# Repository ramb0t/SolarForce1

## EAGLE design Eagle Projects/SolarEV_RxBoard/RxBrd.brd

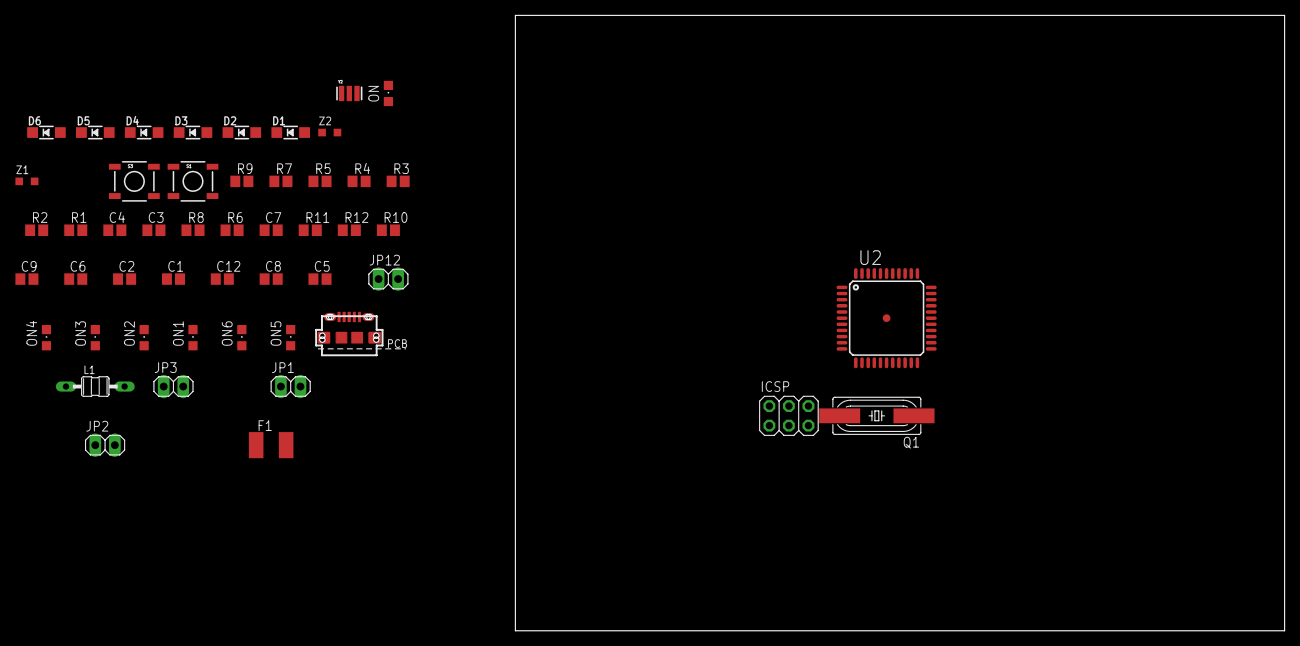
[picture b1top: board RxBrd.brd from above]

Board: 2 copper layers, 100.0 x 80.0 mm, 50 parts (0 on the bottom side), 34 nets, no tracks yet.

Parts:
C1, C2, C6, C9: 100n; C0805
C3, C4: 22p; C0805
C5: 100nF; C0805
C7: 1uF; C0805
C8, C12: 10uF; C0805
D1, D2, D3, D4, D5, D6: MBR0540; SOD123@2
F1: MF-MSMF050-2 500mA; L1812
ICSP: ICSP; 2X03
J1: USB MICRO; CON2_USB_MICRO_B_AT
JP1: Anemometer Connect; 1X02
JP2: PhotovoltaicCell Connect; 1X02
JP3: RF Link Connect; 1X02
JP12: 1X02
L1: 10uH; MMICC7
ON: Red; CHIPLED_0805
ON1, ON2, ON3, ON4: Green; CHIPLED_0805
ON5, ON6: Yellow; CHIPLED_0805
Q1: HC49UP
R1: 1M; R0805
R2, R3, R7, R9, R10, R11, R12: 1k; R0805
R4, R5: 22; R0805
R6: 51k; R0805
R8: 10k; R0805
S1, S3: RESET; TACTILE_SWITCH_SMD
U2: ATMEGA32U4-XUAU; TQFP44-PAD
Y2: 16MHz; RESONATOR
Z1, Z2: CG0603MLC-05E; CT/CN0603

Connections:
+5V: C1.1, C2.1, C12.1, D1.C, D2.C, D3.C, D5.C, JP1.2, JP12.1, L1.1, R2.2, R3.2, R6.2, R7.2, R9.1, R10.1, R11.1, R12.2, U2.2, U2.14, U2.34
ANEMOMETER_CONNECTED_OK: ON2.C, U2.40
AREF: C6.1, U2.42
AVCC: C5.1, L1.2, U2.24, U2.44
D+: J1.P3, R5.1, Z1.1
D-: J1.P2, R4.1, Z2.1
GND: C1.2, C2.2, C3.2, C4.2, C5.2, C6.2, C7.2, C8.2, C9.2, C12.2, D4.A, D6.A, ICSP.6, J1.P5, J1.S1, J1.S2, J1.S3, J1.S4, J1.S5, J1.S6, JP2.2, JP12.2, ON.C, R8.1, S1.1, S1.2, S3.3, S3.4, U2.5, U2.15, U2.23, U2.35, U2.43, Y2.2, Z1.2, Z2.2
MISO: ICSP.1, U2.11
MOSI: ICSP.4, U2.10
unnamed: D3.A, D4.C, JP1.1, U2.25
unnamed: ON3.A, R7.1
unnamed: ON.A, R12.1
unnamed: D5.A, D6.C, JP2.1, U2.30
unnamed: R6.1, S1.3, S1.4, U2.13
unnamed: ON4.A, R9.2
unnamed: JP3.1, U2.20
unnamed: JP3.2, U2.21
unnamed: ON2.A, R3.1
unnamed: D2.A, ICSP.2
unnamed: ON1.A, R2.1
unnamed: ON5.A, R10.2
unnamed: ON6.A, R11.2
unnamed: ICSP.5, S3.1, S3.2
PC_CONNECTED_OK: ON1.C, U2.41
PHOTOCELL_CONNECTED_OK: ON3.C, U2.39
RD+: R5.2, U2.4
RD-: R4.2, U2.3
RF_TRANSCEIVER_CONNECTED_OK: ON4.C, U2.1
SCK: ICSP.3, U2.9
UCAP: C7.1, U2.6
VUSB: C8.1, C9.1, D1.A, F1.1, R8.2, U2.7
XTAL1: C4.1, Q1.1, R1.1, U2.17, Y2.3
XTAL2: C3.1, Q1.2, R1.2, U2.16, Y2.1
XUSB: F1.2, J1.P1

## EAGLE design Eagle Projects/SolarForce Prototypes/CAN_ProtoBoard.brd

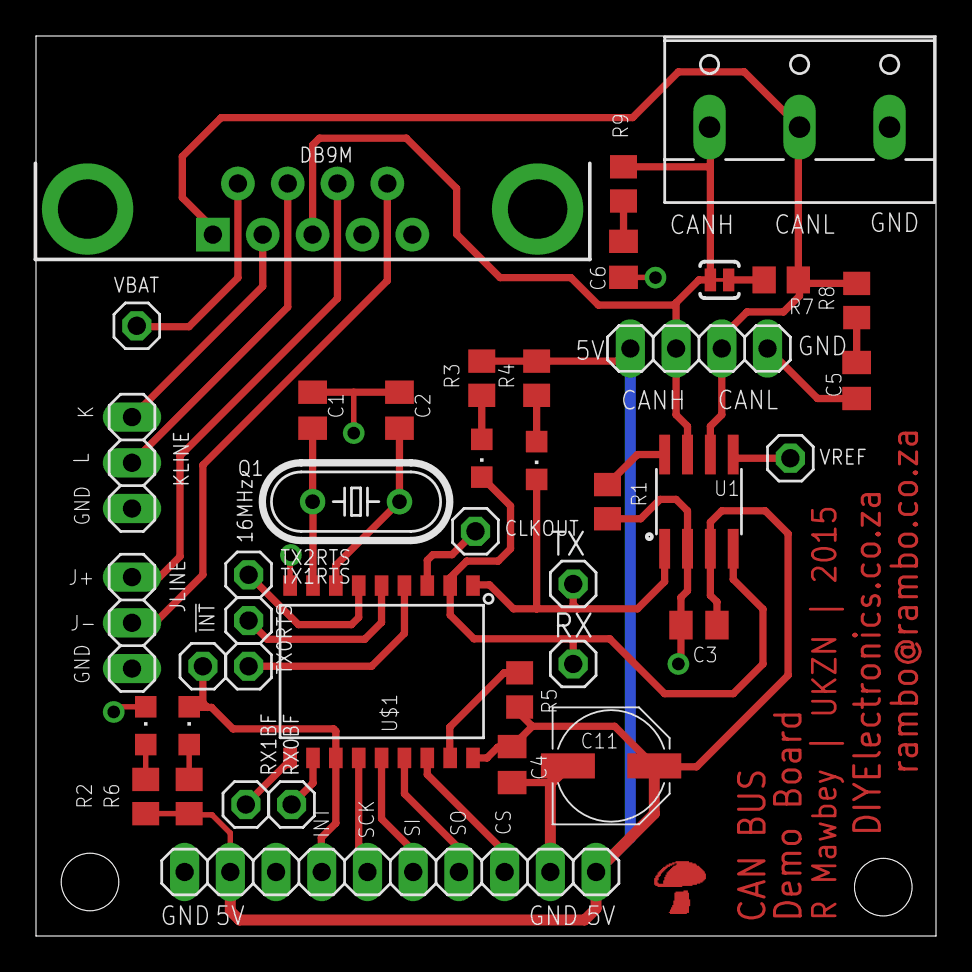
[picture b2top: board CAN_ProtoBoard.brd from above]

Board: 2 copper layers, 50.0 x 50.0 mm, 41 parts (0 on the bottom side), 34 nets.

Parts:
!INT: 1X01
C1, C2: 22pF; C0805K
C3, C4: 100nF; C0805K
C5, C6: 560pF; C0805K
C11: 100uF; PANASONIC_D
CAN: 1X04
CANSCREW: W237-103
CLKOUT: 1X01
DB9M: DB9_MALE
IO: 1X10
JLINE: 1X03
KLINE: 1X03
LED1: PWR; CHIPLED_0805
LED2: RX; CHIPLED_0805
LED3: TX; CHIPLED_0805
LED4: INT; CHIPLED_0805
Q1: 16MHz; HC49/S
R1, R2: R0805
R3, R4, R6: 1k; R0805
R5: 10k; R0805
R7: 120E; R0805
R8, R9: 100E; R0805
RX, RX0BF, RX1BF: 1X01
SJ1: Term; SJ_2S-TRACE
TX, TX0RTS, TX1RTS, TX2RTS: 1X01
U1: MCP2551; SO08
U$1: MCP2515SO; SO-18W
VBAT: 1X01
VREF: 1X01

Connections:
+5V: C3.1, C4.1, C11.+, CAN.4, IO.2, IO.10, R2.2, R3.2, R4.2, R5.2, R6.2, U1.3, U$1.18
CANH: CAN.3, CANSCREW.1, DB9M.3, R9.2, SJ1.1, U1.7
CANL: CAN.2, CANSCREW.2, DB9M.5, R7.2, R8.2, U1.6
CLKOUT: CLKOUT.1, U$1.3
CS: IO.8, U$1.16
GND: C1.1, C2.1, C3.2, C4.2, C5.1, C6.1, C11.-, CAN.1, CANSCREW.3, DB9M.2, IO.1, IO.9, JLINE.1, KLINE.1, LED1.C, R1.2, U1.2, U$1.9
INT: !INT.1, IO.4, LED4.C, U$1.12
J+: DB9M.7, JLINE.3
J-: DB9M.6, JLINE.2
K: DB9M.4, KLINE.3
L: DB9M.8, KLINE.2
unnamed: C1.2, Q1.2, U$1.8
unnamed: C2.2, Q1.1, U$1.7
unnamed: LED2.A, R3.1
unnamed: LED3.A, R4.1
unnamed: R5.1, U$1.17
unnamed: LED1.A, R2.1
unnamed: LED4.A, R6.1
unnamed: R1.1, U1.8
unnamed: R7.1, SJ1.2
unnamed: U1.5, VREF.1
unnamed: C5.2, R8.1
unnamed: C6.2, R9.1
RX0BF: RX0BF.1, U$1.11
RX1BF: RX1BF.1, U$1.10
RXCAN: LED2.C, RX.1, U1.4, U$1.2
SCK: IO.5, U$1.13
SI: IO.6, U$1.14
SO: IO.7, U$1.15
TX0RTS: TX0RTS.1, U$1.4
TX1RTS: TX1RTS.1, U$1.5
TX2RTS: TX2RTS.1, U$1.6
TXCAN: LED3.C, TX.1, U1.1, U$1.1
VBAT: DB9M.9, VBAT.1

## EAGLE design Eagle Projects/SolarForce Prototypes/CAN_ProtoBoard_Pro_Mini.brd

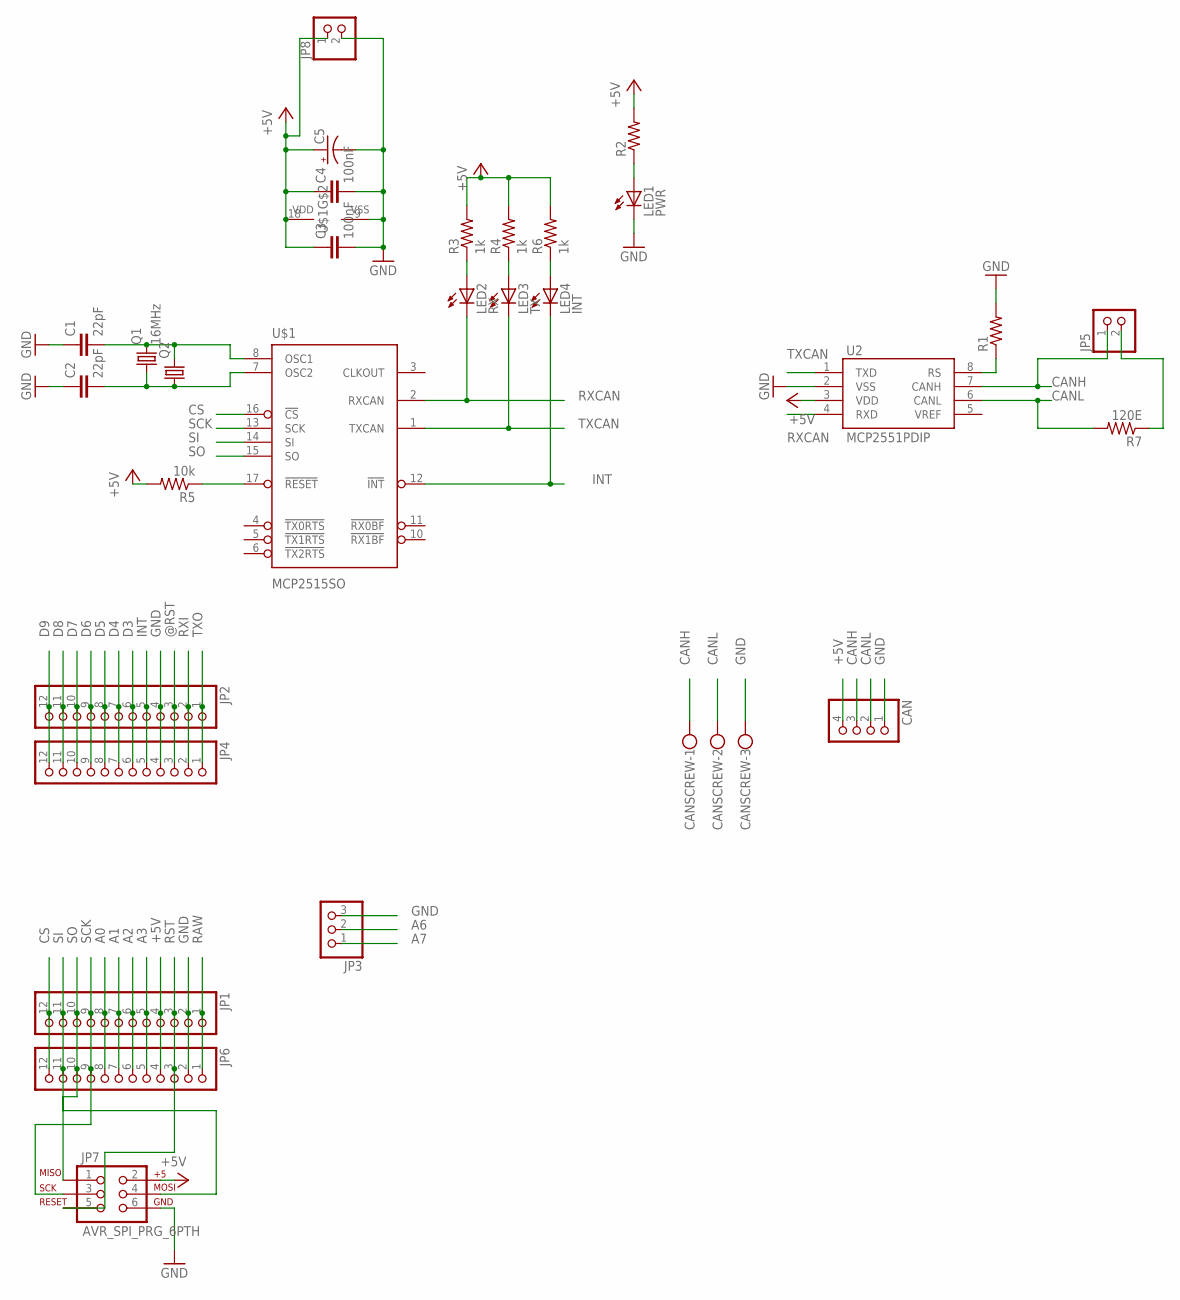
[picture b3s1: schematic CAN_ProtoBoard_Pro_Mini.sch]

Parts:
C1, C2: 22pF; C0805K
C3, C4: 100nF; C0805K
C5: CPOL-USE5-8.5; E5-8,5
CAN: PINHD-1X4; 1X04
CANSCREW: W237-103
JP1, JP2, JP4, JP6: PINHD-1X12; 1X12
JP3: PINHD-1X3; 1X03
JP5, JP8: PINHD-1X2; 1X02
JP7: AVR_SPI_PRG_6PTH; 2X3
LED1: PWR; LED3MM
LED2: RX; LED3MM
LED3: TX; LED3MM
LED4: INT; LED3MM
Q1: 16MHz; HC49/S
Q2: CRYSTALHC49UP; HC49UP
R1, R2: R-US_R0805; R0805
R3, R4, R6: 1k; R0805
R5: 10k; R0805
R7: 120E; R0805
U2: MCP2551PDIP; DIL08
U$1: MCP2515SO; SO-18W

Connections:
+5V: C3.1, C4.1, C5.+, CAN.4, JP1.4, JP6.4, JP7.2, JP8.1, R2.2, R3.2, R4.2, R5.2, R6.2, U2.3 (VDD), U$1.18 (VDD)
@RST: JP2.3, JP4.3
A0: JP1.8, JP6.8
A1: JP1.7, JP6.7
A2: JP1.6, JP6.6
A3: JP1.5, JP6.5
A6: JP3.2
A7: JP3.1
CANH: CAN.3, CANSCREW.1, JP5.1, U2.7 (CANH)
CANL: CAN.2, CANSCREW.2, R7.2, U2.6 (CANL)
CS: JP1.12, JP6.12, U$1.16 (!CS)
D3: JP2.6, JP4.6
D4: JP2.7, JP4.7
D5: JP2.8, JP4.8
D6: JP2.9, JP4.9
D7: JP2.10, JP4.10
D8: JP2.11, JP4.11
D9: JP2.12, JP4.12
GND: C1.1, C2.1, C3.2, C4.2, C5.-, CAN.1, CANSCREW.3, JP1.2, JP2.4, JP3.3, JP4.4, JP6.2, JP7.6, JP8.2, LED1.K (C), R1.2, U2.2 (VSS), U$1.9 (VSS)
INT: JP2.5, JP4.5, LED4.K (C), U$1.12 (!INT)
unnamed: C1.2, Q1.2, Q2.2, U$1.8 (OSC1)
unnamed: C2.2, Q1.1, Q2.1, U$1.7 (OSC2)
unnamed: LED2.A, R3.1
unnamed: LED3.A, R4.1
unnamed: R5.1, U$1.17 (!RESET)
unnamed: LED1.A, R2.1
unnamed: LED4.A, R6.1
unnamed: R1.1, U2.8 (RS)
unnamed: JP5.2, R7.1
RAW: JP1.1, JP6.1
RST: JP1.3, JP6.3, JP7.5
RXCAN: LED2.K (C), U2.4 (RXD), U$1.2 (RXCAN)
RXI: JP2.2, JP4.2
SCK: JP1.9, JP6.9, JP7.3, U$1.13 (SCK)
SI: JP1.11, JP6.11, JP7.4, U$1.14 (SI)
SO: JP1.10, JP6.10, JP7.1, U$1.15 (SO)
TXCAN: LED3.K (C), U2.1 (TXD), U$1.1 (TXCAN)
TXO: JP2.1, JP4.1

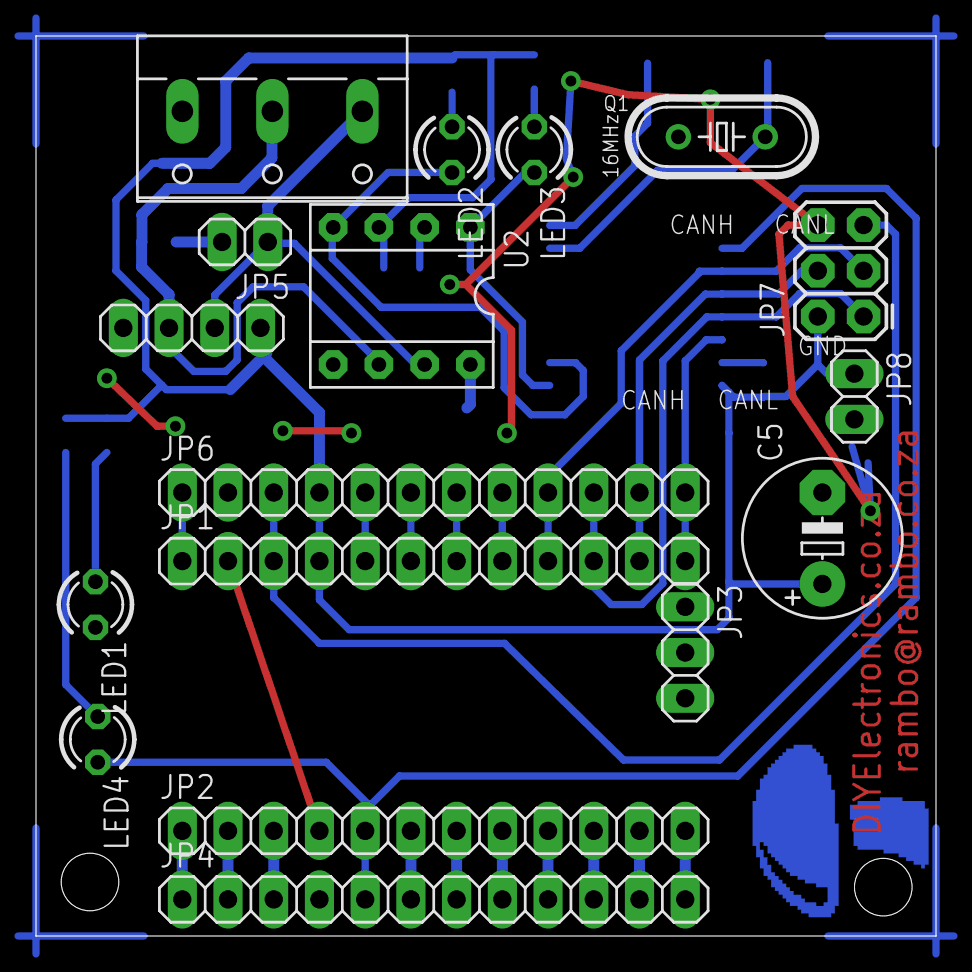
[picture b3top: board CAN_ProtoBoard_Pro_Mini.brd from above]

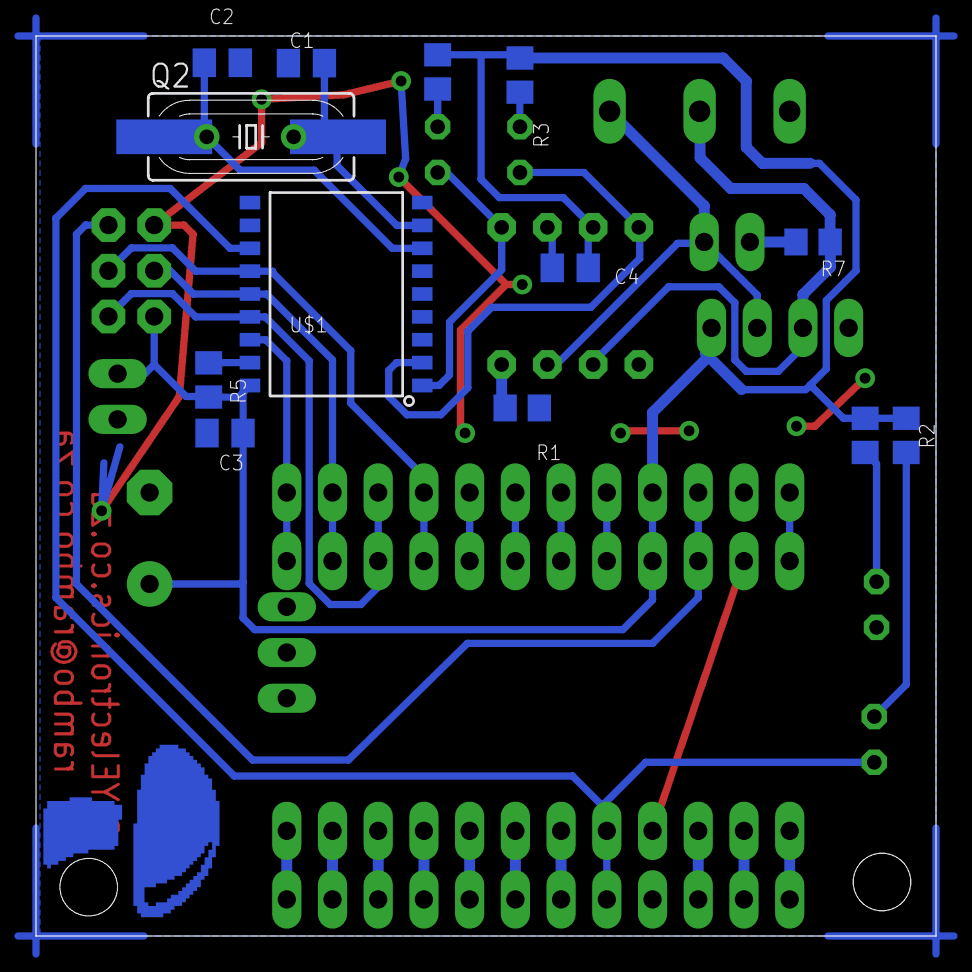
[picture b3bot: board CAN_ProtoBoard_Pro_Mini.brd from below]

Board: 2 copper layers, 50.0 x 50.0 mm, 30 parts (13 on the bottom side), 36 nets.

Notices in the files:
parts and their libraries:
SparkFun: Licensing: CC v3.0 Share-Alike You are welcome to use this library for commercial purposes.
SparkFun-DigitalIC: Licensing: Creative Commons ShareAlike 4.0 International - https://creativecommons.org/licenses/by-sa/4.0
